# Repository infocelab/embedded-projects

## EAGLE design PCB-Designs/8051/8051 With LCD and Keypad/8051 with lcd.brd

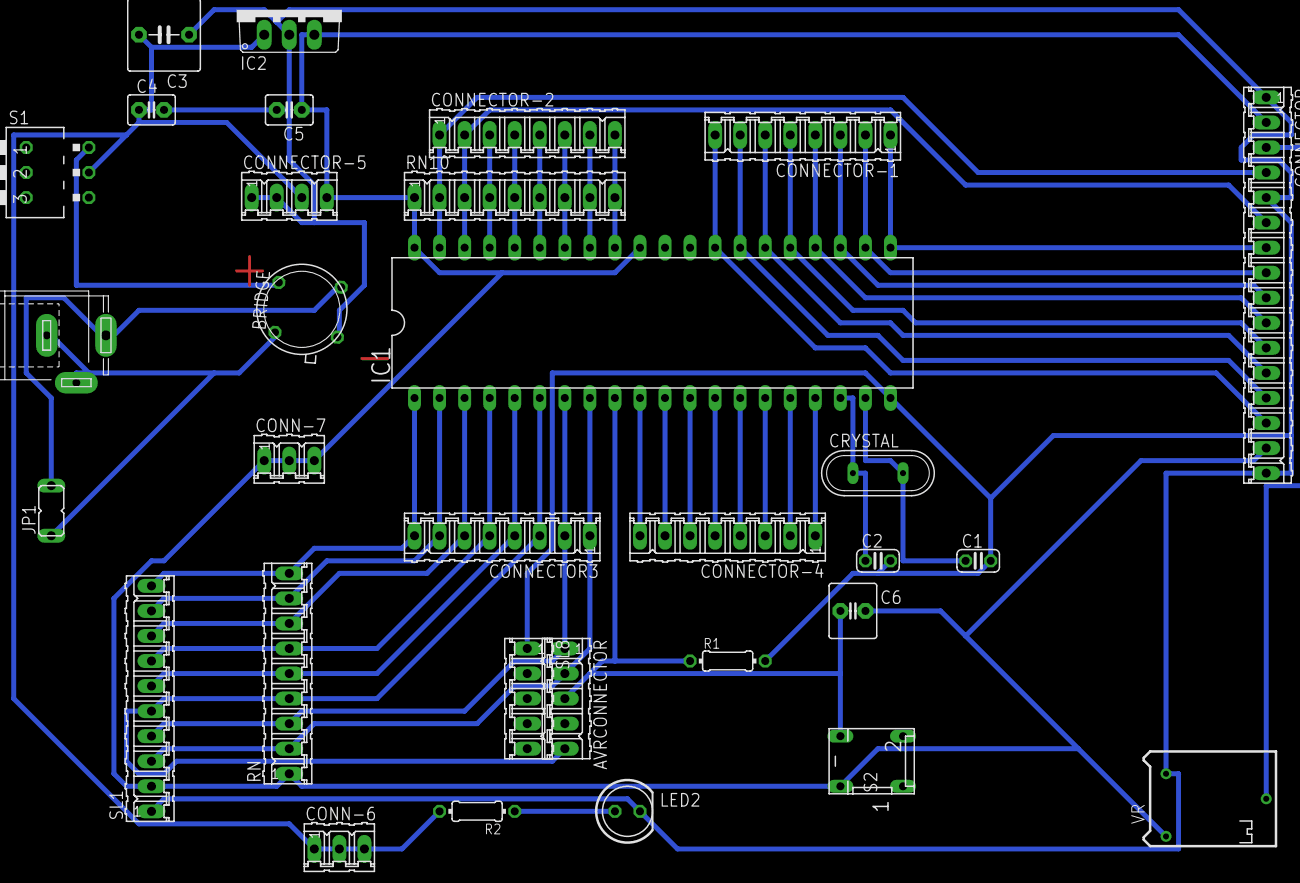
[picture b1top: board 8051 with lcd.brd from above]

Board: 2 copper layers, 31 parts (0 on the bottom side), 43 nets.

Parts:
AVRCONNECTOR: 05P
BRIDGE: TO39/4
C1, C2: 33pf; C025-024X044
C3: 470uf; C5B7.2
C4: .01uf; C2.5-3
C5: 4.7uf; C2.5-3
C6: 0.1uf; C2.5-6
CONN-6, CONN-7: 3 pin; 03P
CONNECTOR: LCD; 16P
CONNECTOR3: 8 pin; 08P
CONNECTOR-1, CONNECTOR-2, CONNECTOR-4: 8 pin; 08P
CONNECTOR-5: 4 pin; 04P
CRYSTAL: 11.0592 mhz; QS
IC1: AT89S51; DIL40
IC2: 7805TV; TO220V
J1: SPC4077
JP1: TRANSFORMER; JP1
LED2: 5mm; LED5MM
R1: 10k; 0204/7
R2: 560E; 0204/7
RN: 10K; 09P
RN10: 10 k; 09P
S1: ON/ OFF SWITCH; DA-03
S2: push switch; DP-02
SL1: keypad; 10P
SL8: 05P
VR: 10k; RTRIM64P

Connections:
unnamed: C2.1, CRYSTAL.1, IC1.18
unnamed: C1.1, CRYSTAL.2, IC1.19
unnamed: C3.2, C4.1, CONN-6.1, CONN-6.2, CONN-6.3, CONNECTOR-5.3, IC2.1, R2.2, S1.5
unnamed: BRIDGE.2, J1.3, JP1.2
unnamed: CONNECTOR-4.8, IC1.10
unnamed: CONNECTOR-4.7, IC1.11
unnamed: CONNECTOR-4.6, IC1.12
unnamed: CONNECTOR-4.5, IC1.13
unnamed: CONNECTOR-4.4, IC1.14
unnamed: CONNECTOR-4.3, IC1.15
unnamed: CONNECTOR-4.2, IC1.16
unnamed: CONNECTOR-4.1, IC1.17
unnamed: AVRCONNECTOR.3, C6.1, IC1.9, R1.1, S2.3
unnamed: AVRCONNECTOR.1, CONNECTOR3.2, IC1.7, RN.3, SL1.4
unnamed: BRIDGE.4, J1.1, J1.2, JP1.1
unnamed: CONNECTOR3.4, IC1.5, RN.5, SL1.6
unnamed: CONNECTOR3.5, IC1.4, RN.6, SL1.7
unnamed: CONNECTOR3.6, IC1.3, RN.7, SL1.8
unnamed: CONNECTOR3.7, IC1.2, RN.8, SL1.9
unnamed: CONNECTOR3.8, IC1.1, RN.9, SL1.10
unnamed: CONNECTOR-2.3, IC1.37, RN10.4
unnamed: CONNECTOR-2.4, IC1.36, RN10.5
unnamed: CONNECTOR-2.5, IC1.35, RN10.6
unnamed: CONNECTOR-2.6, IC1.34, RN10.7
unnamed: CONNECTOR-2.7, IC1.33, RN10.8
unnamed: CONNECTOR-2.8, IC1.32, RN10.9
unnamed: CONNECTOR.7, CONNECTOR-1.1, IC1.21
unnamed: CONNECTOR.8, CONNECTOR-1.2, IC1.22
unnamed: CONNECTOR.9, CONNECTOR-1.3, IC1.23
unnamed: CONNECTOR.12, CONNECTOR-1.6, IC1.26
unnamed: CONNECTOR.3, VR.2
unnamed: C5.1, C6.2, CONN-7.1, CONN-7.2, CONN-7.3, CONNECTOR.2, CONNECTOR.15, CONNECTOR-5.4, IC1.31, IC1.40, IC2.3, RN.1, RN10.1, S2.4, SL1.2, VR.1
unnamed: BRIDGE.1, C1.2, C2.2, C3.1, C4.2, C5.2, CONNECTOR.1, CONNECTOR.5, CONNECTOR.16, CONNECTOR-5.1, CONNECTOR-5.2, IC1.20, IC2.2, LED2.K, R1.2, SL1.1, SL8.1, VR.3
unnamed: AVRCONNECTOR.5, CONNECTOR3.3, IC1.6, RN.4, SL1.5
unnamed: LED2.A, R2.1
unnamed: AVRCONNECTOR.2, CONNECTOR3.1, IC1.8, RN.2, SL1.3
unnamed: BRIDGE.3, S1.6
unnamed: CONNECTOR.6, CONNECTOR-2.2, IC1.38, RN10.3
unnamed: CONNECTOR.10, CONNECTOR-1.4, IC1.24
unnamed: CONNECTOR.11, CONNECTOR-1.5, IC1.25
unnamed: CONNECTOR.13, CONNECTOR-1.7, IC1.27
unnamed: CONNECTOR.14, CONNECTOR-1.8, IC1.28
unnamed: CONNECTOR.4, CONNECTOR-2.1, IC1.39, RN10.2

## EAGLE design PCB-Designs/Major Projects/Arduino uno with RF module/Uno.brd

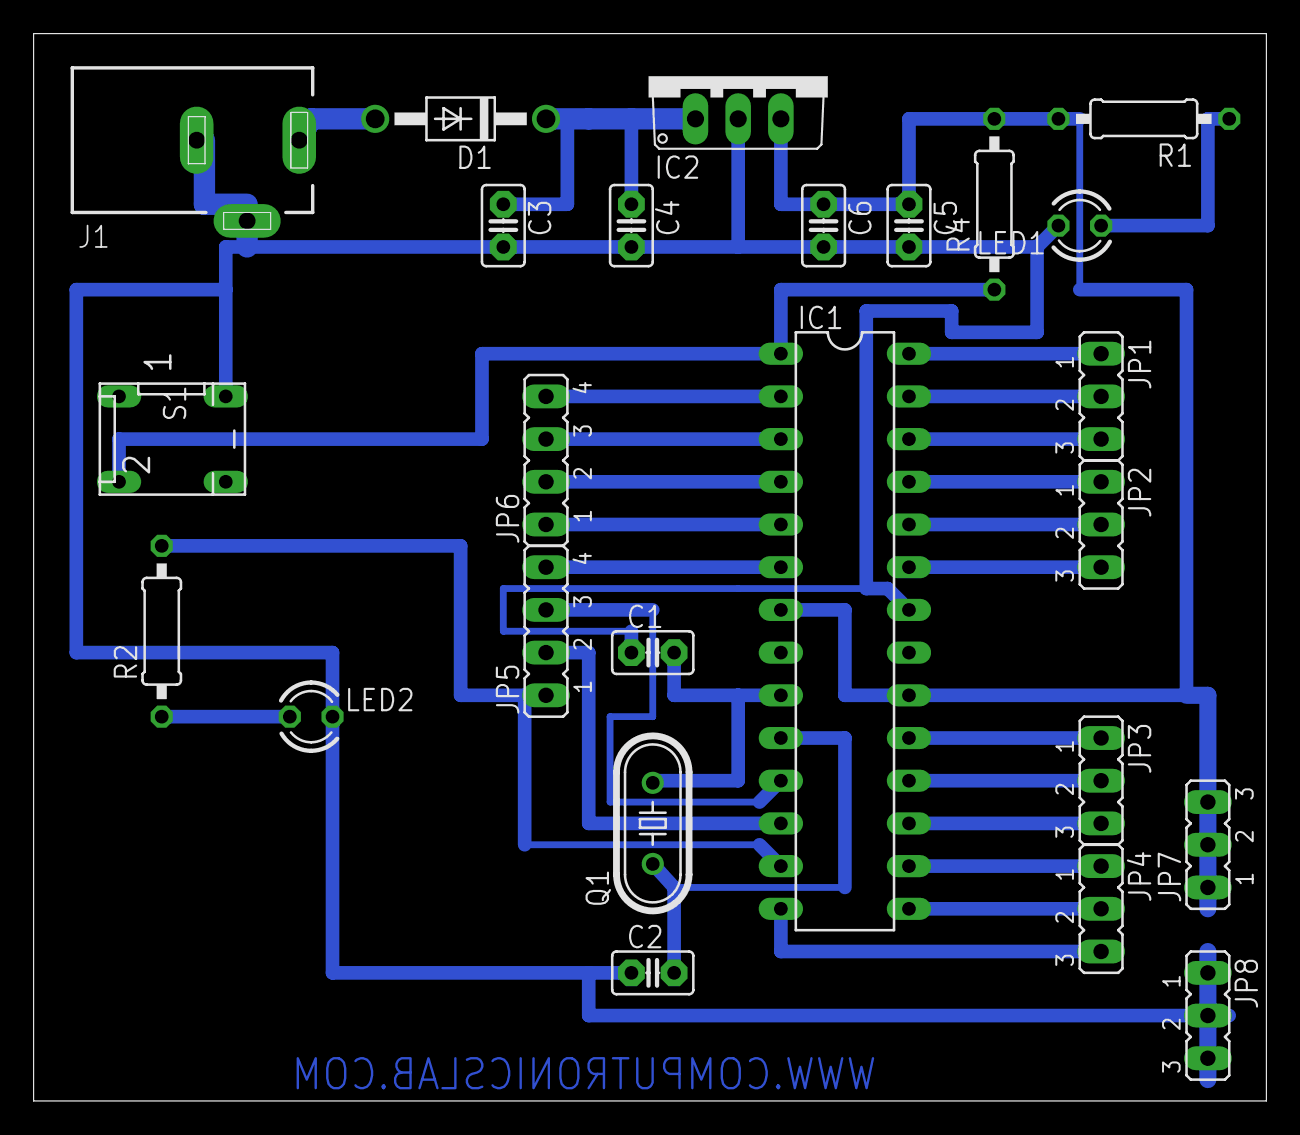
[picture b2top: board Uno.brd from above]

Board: 2 copper layers, 73.3 x 63.5 mm, 25 parts (0 on the bottom side), 29 nets.

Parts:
C1, C2: 22pf; C2.5-2
C3: 100UF; C2.5-2
C4, C5: 0.1uf; C2.5-2
C6: 4.7uf; C2.5-2
D1: 1N4007; DO41-10
IC1: ATMEGA328; DIL28-3
IC2: 7805; TO220V
J1: DCJ0303
JP1, JP2, JP3, JP4, JP7, JP8: JP2
JP5, JP6: JP4
LED1, LED2: LED3MM
Q1: 12MHZ; HC49/S
R1: 220R; 0207/10
R2: 330R; 0207/10
R4: 10K; 0207/10
S1: DP-02

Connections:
unnamed: C1.2, IC1.9, Q1.2
unnamed: C2.2, IC1.10, Q1.1
unnamed: D1.A, J1.1
unnamed: C5.1, C6.1, IC1.7, IC1.20, IC2.3, R1.2, R4.2
unnamed: C1.1, C2.1, C3.2, C4.2, C5.2, C6.2, IC1.22, IC2.2, J1.2, J1.3, LED1.K, LED2.K, S1.4
unnamed: LED1.A, R1.1
unnamed: C3.1, C4.1, D1.C, IC2.1
unnamed: IC1.28, JP1.1
unnamed: IC1.27, JP1.2
unnamed: IC1.26, JP1.3
unnamed: IC1.25, JP2.1
unnamed: IC1.24, JP2.2
unnamed: IC1.23, JP2.3
unnamed: IC1.5, JP6.1
unnamed: IC1.2, JP6.4
unnamed: IC1.3, JP6.3
unnamed: IC1.4, JP6.2
unnamed: IC1.6, JP5.4
unnamed: IC1.12, JP5.2
unnamed: IC1.11, JP5.3
unnamed: IC1.13, JP5.1, R2.2
unnamed: IC1.14, JP4.3
unnamed: IC1.15, JP4.2
unnamed: IC1.16, JP4.1
unnamed: IC1.17, JP3.3
unnamed: IC1.18, JP3.2
unnamed: IC1.19, JP3.1
unnamed: IC1.1, R4.1, S1.2
unnamed: LED2.A, R2.1

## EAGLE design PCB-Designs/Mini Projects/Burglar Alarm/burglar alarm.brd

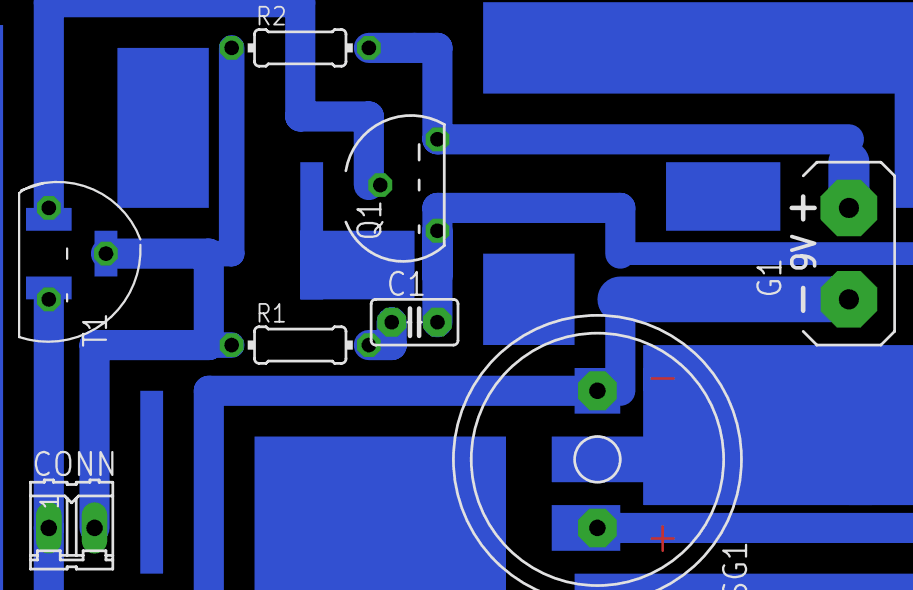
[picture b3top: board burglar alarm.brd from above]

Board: 2 copper layers, 8 parts (0 on the bottom side), 6 nets.

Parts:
C1: 0.1UF; C2.5-2
CONN: 2 PIN; 02P
G1: AB9V
Q1: BC557; TO92
R1, R2: 10k; 0204/7
SG1: BUZZER; F/QMB
T1: BC547; TO92

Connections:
unnamed: C1.2, Q1.3, SG1.+
unnamed: C1.1, R1.2
unnamed: CONN.1, G1.-, SG1.-, T1.1
unnamed: CONN.2, R1.1, R2.1, T1.2
unnamed: G1.+, Q1.1, R2.2
unnamed: Q1.2, T1.3

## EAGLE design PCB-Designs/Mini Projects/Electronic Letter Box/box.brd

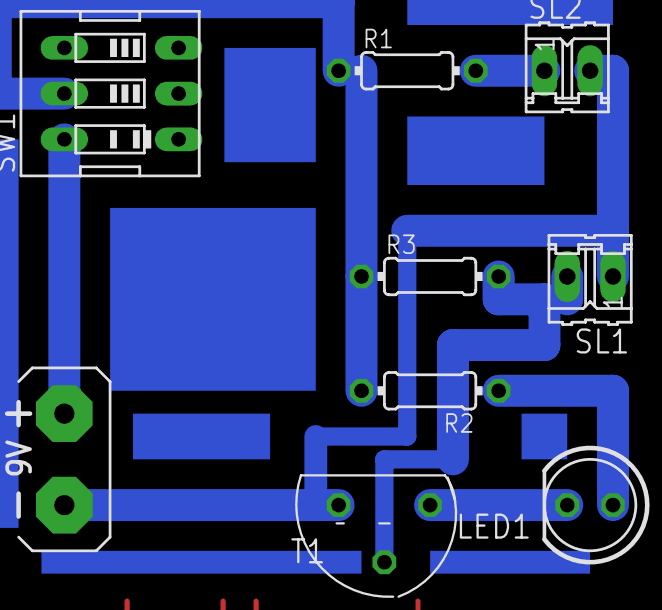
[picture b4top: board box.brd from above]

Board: 2 copper layers, 9 parts (0 on the bottom side), 7 nets.

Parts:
G1: AB9V
LED1: 5mm; LED5MM
R1: 330E; 0204/7
R2: 220E; 0204/7
R3: 100k; 0204/7
SL1: LDR; 02P
SL2: LED; 02P
SW1: on/off button; EDG-03
T1: BC547; TO92

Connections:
unnamed: G1.+, SW1.6
unnamed: G1.-, SL1.1, SL2.2, T1.1
unnamed: R3.2, SL1.2, T1.2
unnamed: R1.2, SL2.1
unnamed: LED1.K, T1.3
unnamed: LED1.A, R2.1
unnamed: R1.1, R2.2, R3.1, SW1.5

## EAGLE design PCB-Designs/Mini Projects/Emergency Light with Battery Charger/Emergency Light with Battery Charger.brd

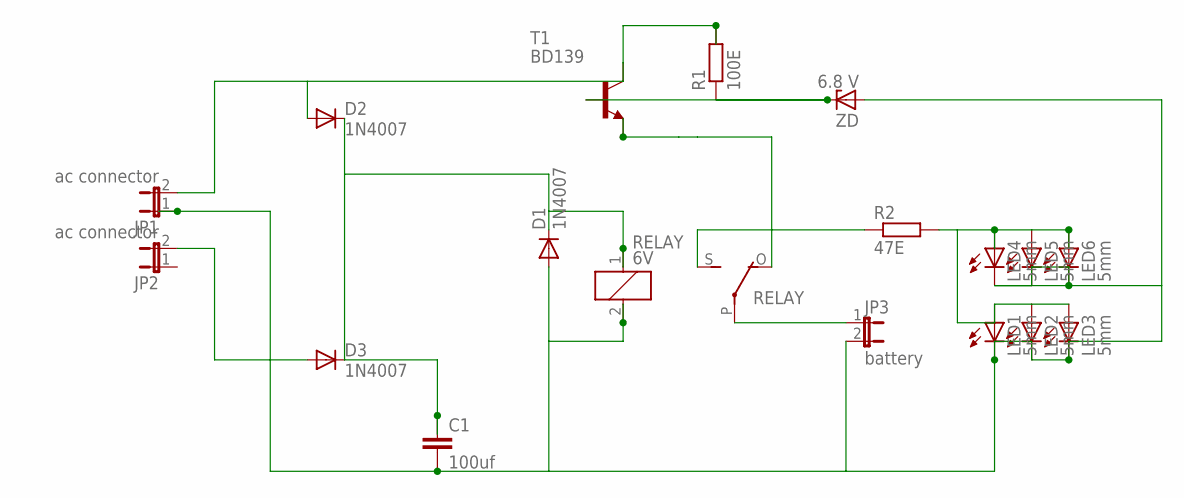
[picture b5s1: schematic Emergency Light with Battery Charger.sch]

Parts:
C1: 100uf; C2.5-5
D1, D2, D3: 1N4007; DO41-10
JP1, JP2: ac connector; JP1
JP3: battery; JP1
LED1, LED2, LED3, LED4, LED5, LED6: 5mm; LED5MM
R1: 100E; 0204/7
R2: 47E; 0204/7
RELAY: 6V; G5LE
T1: BD139; TO126
ZD: 6.8 V; DO35Z10

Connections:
unnamed: D2.A, JP1.2, R1.2, T1.2 (C)
unnamed: D3.A, JP2.2
unnamed: C1.1, D1.C, D2.C, D3.C, RELAY.1
unnamed: C1.2, D1.A, JP1.1, JP3.2, LED1.K (C), LED2.K (C), LED3.K (C), LED4.K (C), LED5.K (C), LED6.K (C), RELAY.2, ZD.A
unnamed: R1.1, T1.3 (B), ZD.C
unnamed: RELAY.O, T1.1 (E)
unnamed: JP3.1, RELAY.P
unnamed: R2.1, RELAY.S
unnamed: LED1.A, LED2.A, LED3.A, LED4.A, LED5.A, LED6.A, R2.2

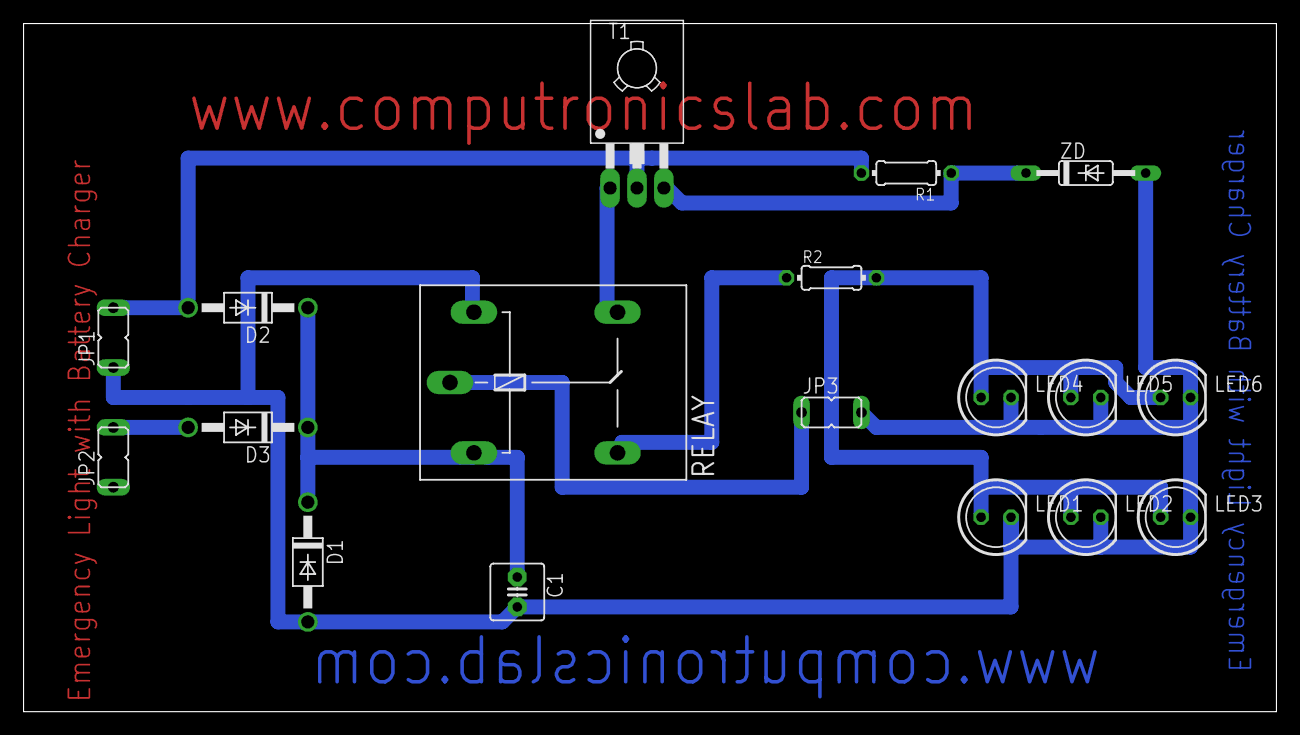
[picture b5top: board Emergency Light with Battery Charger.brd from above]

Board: 2 copper layers, 106.3 x 58.4 mm, 18 parts (0 on the bottom side), 9 nets.

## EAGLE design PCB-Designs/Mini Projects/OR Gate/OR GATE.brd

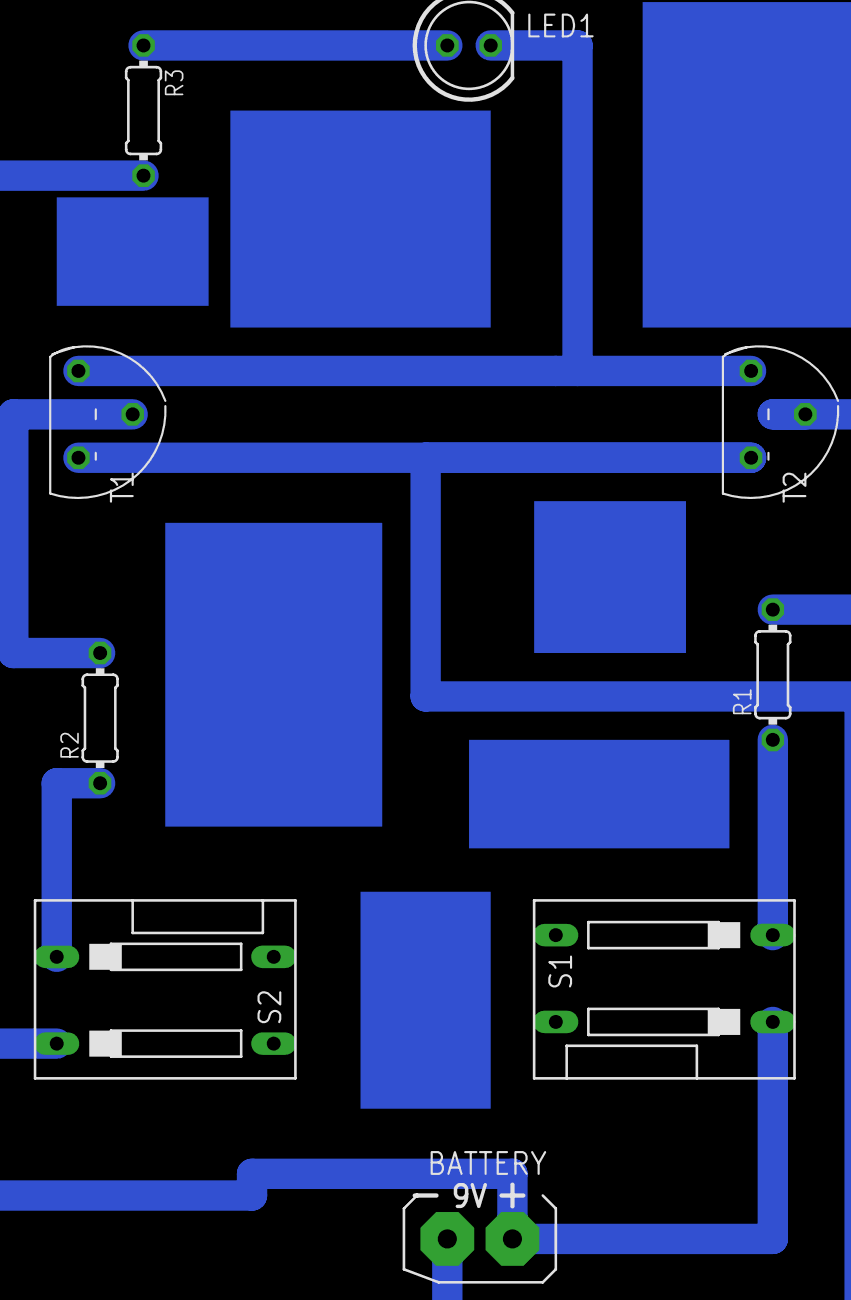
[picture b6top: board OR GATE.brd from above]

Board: 2 copper layers, 9 parts (0 on the bottom side), 8 nets.

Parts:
BATTERY: 9V; AB9V
LED1: 5MM; LED5MM
R1, R2: 10K; 0204/7
R3: 330E; 0204/7
S1, S2: PUSH SWITCH; DS-02
T1, T2: BC547; TO92

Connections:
unnamed: LED1.K, T1.3, T2.3
unnamed: R1.2, T2.2
unnamed: R2.2, T1.2
unnamed: LED1.A, R3.1
unnamed: R1.1, S1.2
unnamed: R2.1, S2.1
unnamed: BATTERY.+, R3.2, S1.1, S2.2
unnamed: BATTERY.-, T1.1, T2.1

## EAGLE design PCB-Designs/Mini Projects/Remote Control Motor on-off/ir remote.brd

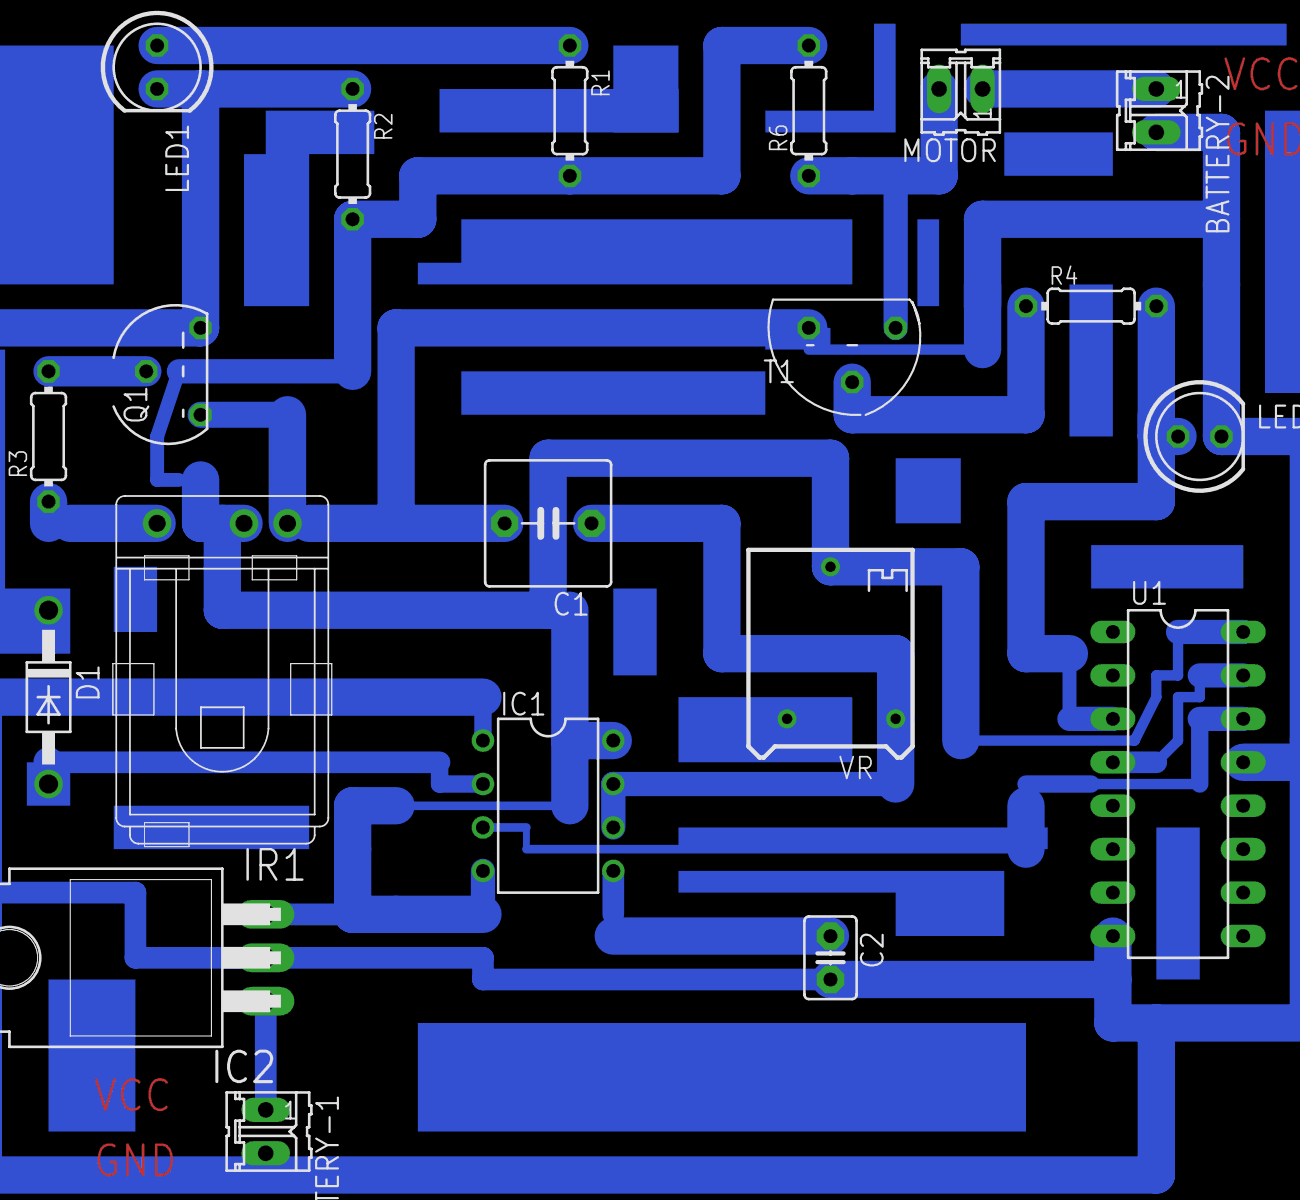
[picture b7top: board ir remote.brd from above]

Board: 2 copper layers, 20 parts (0 on the bottom side), 16 nets.

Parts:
BATTERY-1: 9V; 02P
BATTERY-2: 02P
C1: 100uf; C5B7.2
C2: .01uf; C2.5-3
D1: 1N4007; DO41-10
IC1: NE555; DIL08
IC2: 7805T; TO220H
IR1: TSOP1730TB1; TSOP17_TB1
LED1, LED2: 5MM; LED5MM
MOTOR: 02P
Q1: BC557; TO92
R1, R4: 220E; 0204/7
R2, R6: 10K; 0204/7
R3: 1K; 0204/7
T1: BC547; TO92
U1: IC4017; DIL16
VR: 100K; RTRIM64P

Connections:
unnamed: C1.1, IC1.6, IC1.7, VR.1
unnamed: LED2.A, R4.2, U1.3
unnamed: BATTERY-1.2, BATTERY-2.2, C1.2, C2.2, IC1.1, IC2.2, IR1.GND, LED2.K, Q1.3, T1.1, U1.8, U1.13
unnamed: D1.A, IC1.2
unnamed: IR1.VO, R3.1
unnamed: Q1.2, R3.2
unnamed: C2.1, IC1.5
unnamed: U1.4, U1.15
unnamed: IC1.4, IC1.8, IC2.3, IR1.VS, R1.2, R2.2, R6.2, U1.16, VR.2
unnamed: LED1.A, R1.1
unnamed: D1.C, LED1.K, Q1.1, R2.1
unnamed: R4.1, T1.2
unnamed: MOTOR.2, R6.1, T1.3
unnamed: BATTERY-2.1, MOTOR.1
unnamed: IC1.3, U1.14
unnamed: BATTERY-1.1, IC2.1

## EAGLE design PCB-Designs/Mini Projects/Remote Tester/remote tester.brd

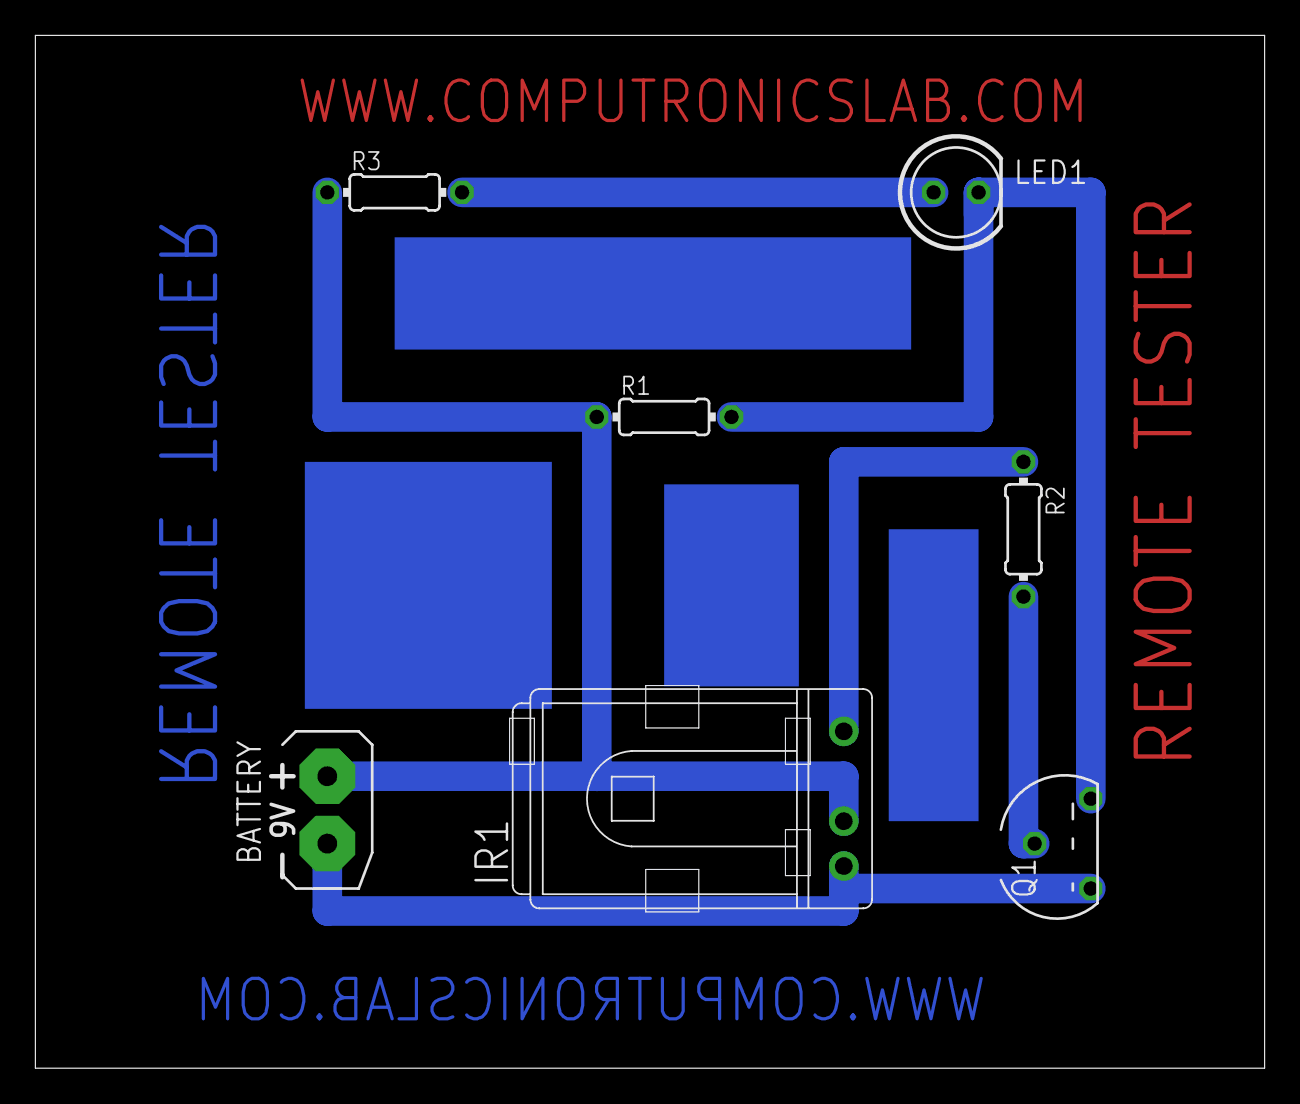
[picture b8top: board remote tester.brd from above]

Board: 2 copper layers, 69.5 x 58.4 mm, 7 parts (0 on the bottom side), 6 nets.

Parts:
BATTERY: 9V; AB9V
IR1: TSOP1738; TSOP17_TB1
LED1: 5mm; LED5MM
Q1: BC557; TO92
R1: 10k; 0204/7
R2: 1k; 0204/7
R3: 220E; 0204/7

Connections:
unnamed: BATTERY.+, IR1.VS, R1.1, R3.1
unnamed: BATTERY.-, IR1.GND, Q1.3
unnamed: LED1.A, R3.2
unnamed: Q1.2, R2.2
unnamed: LED1.K, Q1.1, R1.2
unnamed: IR1.VO, R2.1
